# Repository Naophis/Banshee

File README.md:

# Banshee
 
2022年全日本大会で突貫で2セル化したExiaSnowWhiteをベースに、正式な2セル機として作成したシリーズ。  
ExiaSnowWhiteでは電源周りのノイズに苦戦した反省から回路の見直しを実施。  
足回りについてはマイクロマウス合宿で発表した「ベアリングホルダー方式」を採用することで、足回りの剛性を強化。高速走行時の安定性につなぐことができた機体です。

このリポジトリでは、Bansheeで利用しているすべてのソースコードと基板のファイルを公開しています。

## 利用部品解説

### 1. CPU
ESP32-S3の以下の型番を利用
* ESP32-S3-FH4R2 (Banshee/BansheeAlter)
* ESP32-S3-PICO-1 (Banshee.SSS)

上記の2モデルは昨年発売されておらず、今シーズンから採用。  
昨年使用していたESP32-S3-FN8との違いはPSRAMが搭載で、2MBまでログを取得できるようになったことで細かい解析ができるようになった。

ESP32-PICO-1ではオシレーターの内蔵版となったことで部品点数削減につながった。

画像の通りパッドに違いがある。

#### 1.1 困ったこと
#### 1.1.1 FreeRTOSの固着
ESP32-S3ではデータシートにオシレーターの推奨回路が提示されているが、そのとおり実装すると、モーターを高Dutyで回した際に、FreeRTOSが停止するという問題が発生、推奨回路のコンデンサを除去することで解決した。

#### 1.1.2 データシートにないピンの初期値High問題
書き込み時、電源投入時にHighを出力するピンが存在した。  
ESP32の他シリーズではデータシートに記載しているものもあるがS3では未記載である。
モータードライバにつながったピンに利用すると書き込み時にDuty100%で回転するなど、運用面の問題が発生するため回路の作り直しにつながった。

以下が問題のピン
* PIN26: GPIO20
* PIN28: GPIO26
* PIN44: GPIO39
> 他にもある可能性があり。

### 2. MotorDriver
* DRV8835  (Banshee/BansheeAlter)
* TB6614FNG (Banshee.SSS)

#### 2.1 DRV8835
多くの機体で採用されているが、その理由は以下の通り。
1. 小型ながら2A出力できるため、パフォーマンスが高い。
2. 内部抵抗が300mΩと低い
3. スイッチング周波数が最大250kHzと高く、モーターの特性に対応しやすい。
4. dead timeが100nsecと短いため、高めのPWM周波数に対応しやすい。
dead timeについては、大きい場合High-Lowの切り替えに時間がかかりすぎ、何も出力できないということがあり得る。同社の別のモータードライバでは同じような使い方をするとモーターが回らないということがあり得る。

しかし、最大定格が12Vまでであることから、3セルには対応できないため、TB6614FNGに切り替えた。

### 2.2 TB6614GNG
ディスコン部品であり、パッケージもSOP16と大きいが採用理由は以下の通り。
1. 定格が15Vと3セルに対応
2. 出力が瞬間最大4.5Aまで出力できる
3. スイッチング周波数が400kHzと非常に高く、モーターの特性に対応しやすい
4. dead timeが80nsecと短い

3セル化に伴い、クラシックで利用実績があったICであり、パワー勝負するために信頼できることから採用した。

### 3. PowerSupply
#### 3.1 LXDC55
2セル、3セルから直接3.3Vを取得する場合損失が大きく、熱による影響と効率の観点からDCDCコンバータを採用。入力側に容量が大きいコンデンサをつけないとノイズが乗りやすいため、高分子タンタルコンデンサを複数搭載することでノイズ問題は解決した。

> 約4.2Vを出力するよう、500Ωを利用。  

秋月にて購入できるため採用。

#### 3.2 MIC5319-3.3YM5
3.3V出力に利用。LEDの出力を大きくしたため、500mA出力できるこのICを採用。
データシート通りバイパス用のピンに470pFのコンデンサをつけることでノイズの低減効果がある。

秋月にて購入できるため採用。

### 4. LED + PhotoTransistor
* LED:
  * OSI5FU3A11C
  * VSLY5940
* PhotoTransistor: 
  * LTR-4206E

BCR421UFD（定電流回路）を使うことで安定したセンシングを狙っていたが、
昨年の全日本大会では会場の照明が近いことから、環境ノイズの影響を大きく受けた。  
今年も同じ会場になることから、SN比が良くなるよう、高出力化できる＋LTR-4206Eの帯域に合う大型LEDを採用した

#### 5. gyro
LSM6DSRXTRを採用。4000deg/sec対応している点、昨年のExiaSnowWhiteから継続採用

#### 6. encoder
AS5147Pを採用。14bit対応+28000RPMまで対応しているため継続採用。

ベアリングホルダー方式ではエンコーダ基板に穴を開けることで位置決めしやすいした。

## システム解説

Espressif社がESP32向けにカスタムしたFreeRTOSを利用。  
マイクロマウスでは一定周期で実行したい処理と非同期で実行したい処理が大きく分かれる、これらが混在すると周期に乱れが生じてしまう。ESP32-S3はCPUを2コア搭載していることから、物理的に分けて処理することでシステム全体を滞りなく動かすことを狙った設計となっている。

### 工夫
リアルタイムOSを利用しているとはいえ、タスクの優先順位次第では一定周期で処理できないことがある。特にエンコーダは前回値との差を使い速度を算出するため時刻差の影響を大きく受けた。

対策として、前回取得した時刻を記憶、現在時刻との差分から速度、距離の算出に利用したことで制御・判断の精度向上した。

### 課題

上記の画像は上側がplanning_task、下側がsensing_taskの処理時間(μsec)のログである。  
特にsensing_taskでは、定期的に1000μsecを大きく超え、周期が安定しないときが見られる。
また、planningのタスクの優先度を高く設定しているため、安定しているように見える。

原因は2つ判明しており、  
1つ目はmain_taskから要求される指示メッセージの処理不可が大きい点  
2つ目はセンサーに使用するAD変換に時間がかかる点  
である。

メッセージの送信自体が重くデータは構造体ではなく、ポインタを送信しているためデータ量に起因するものではないため、改善が難しい。
AD変換もESP32自体がIoT向けのマイコンである点からあまり得意でないことから改善が不可能である。

AD変換については、常にすべてのAD変換を行うのではなく、重要度の低いものは１回おきに取得することでシステム全体の負荷を下げるなどの工夫はしているが不十分な状況である。

いずれも今後発売予定のESP32-P4による性能向上に伴う改善を期待する。

## change log
1. Banshee
2. Banshee Alter
3. ~~(BansheeNorn)~~
4. Banshee.SSS　(latest)

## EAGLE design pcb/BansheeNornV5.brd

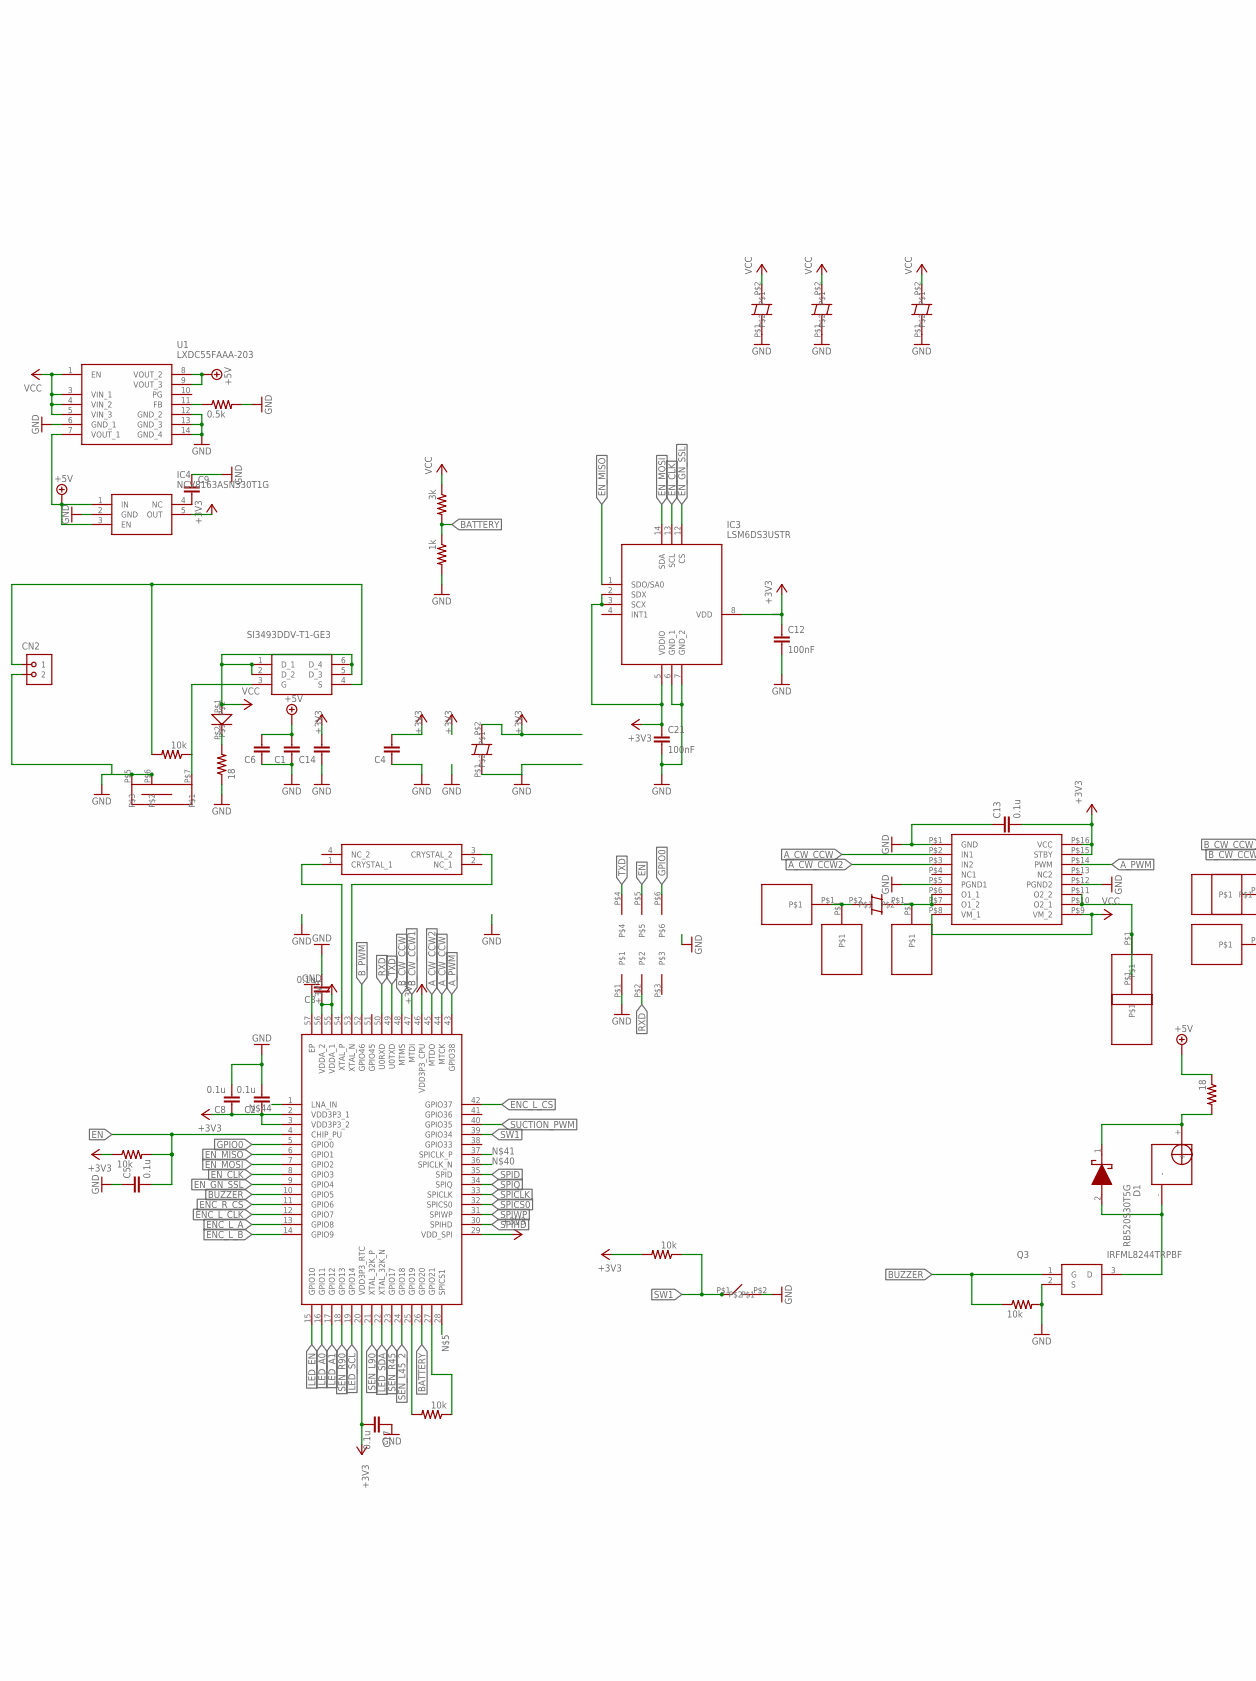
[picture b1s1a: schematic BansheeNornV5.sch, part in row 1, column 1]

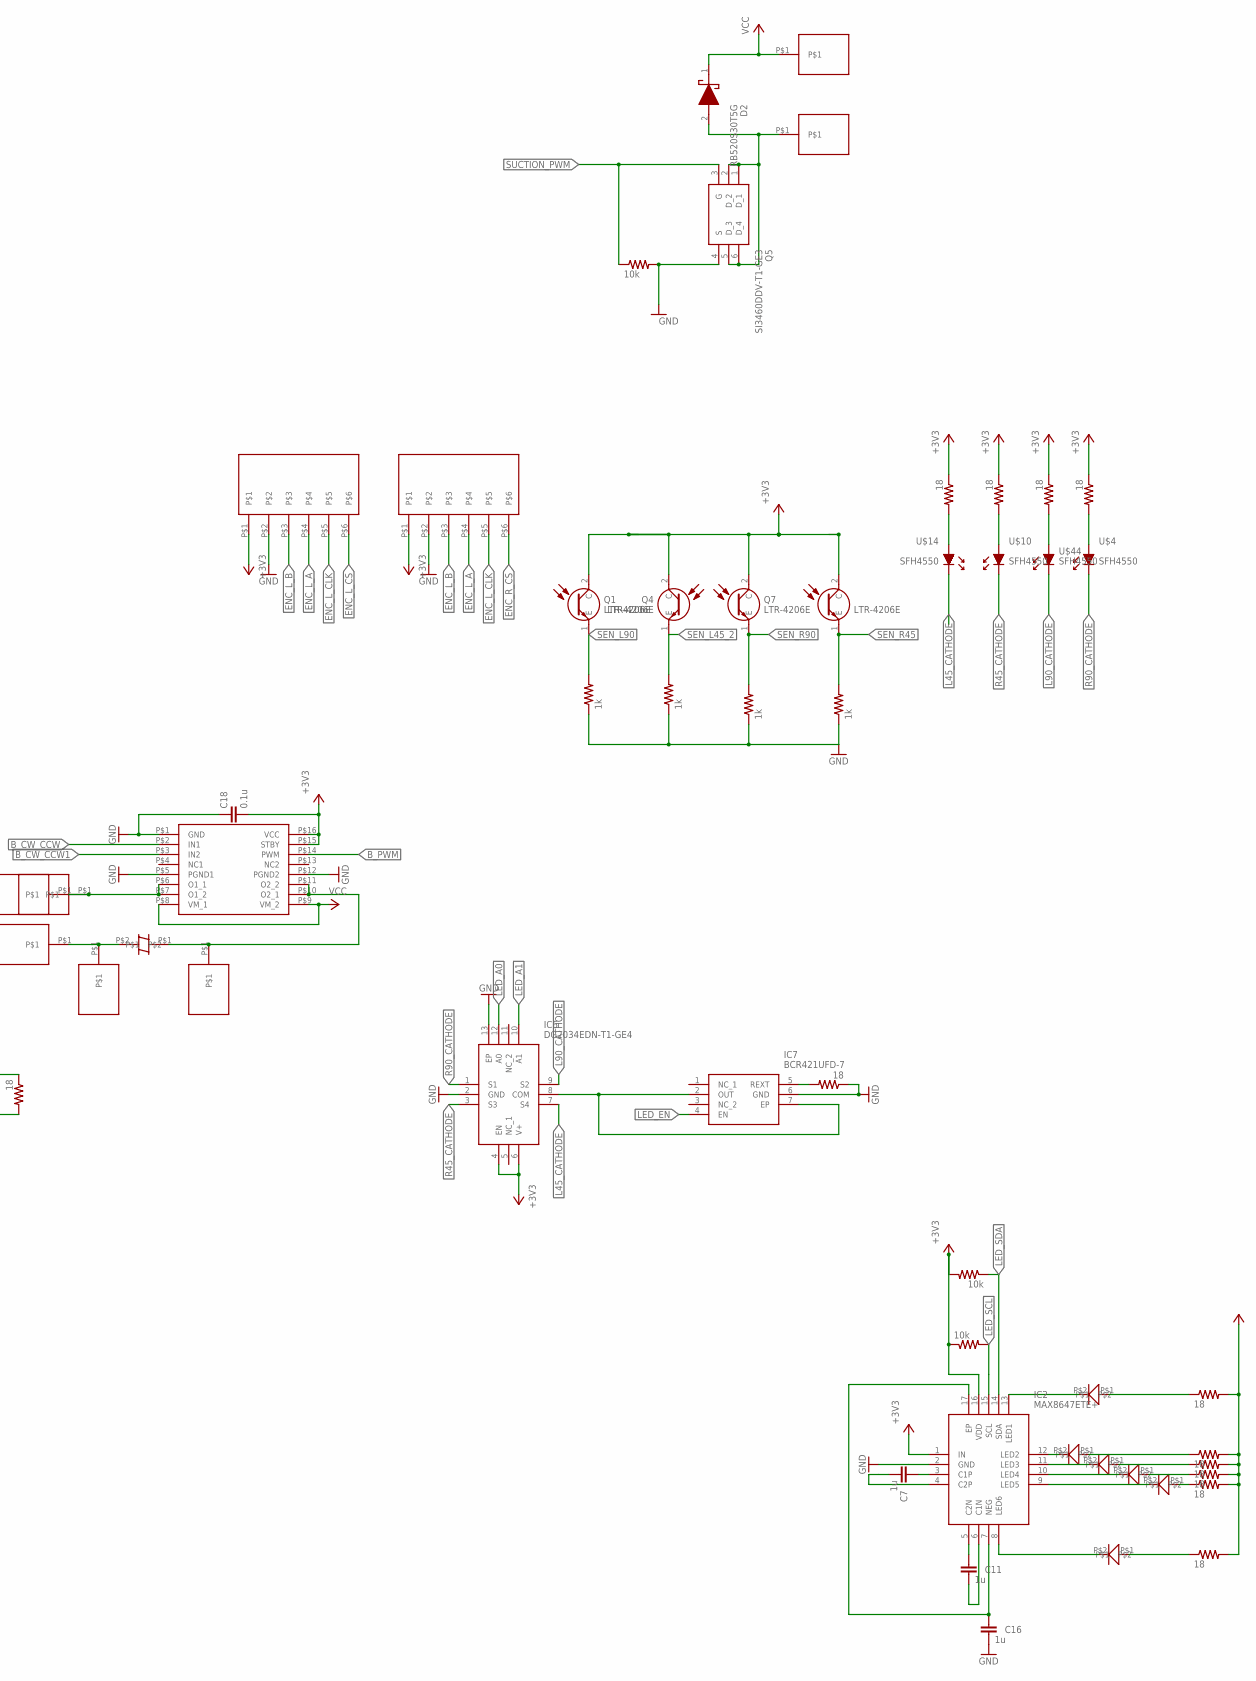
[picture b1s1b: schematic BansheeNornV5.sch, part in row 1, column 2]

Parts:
C1, C4, C6, C14: C3216
C2, C3, C5, C8, C13, C17, C18: 0.1u; R1005
C7, C11, C16: 1u; R1005
C9: C1608
C12, C21: 100nF; R1005
CN2: HRCON-2
D1, D2: RB520S30T5G; SODFL1608X70N
IC1: ESP32-S3-WROOM-1-N8; QFN40P700X700X90-57N
IC2: MAX8647ETE+; QFN50P300X300X80-17N
IC3: LSM6DS3USTR; LGA-14(2.5X3X0.86)
IC4: NCV8163ASN330T1G; SOT95P275X110-5N
IC6: DG2034EDN-T1-GE4; QFN50P300X300X100-13N
IC7: BCR421UFD-7; BCR421UFD7
Q1, Q4, Q7, Q8: LTR-4206E; LTR4206E
Q2: SI3493DDV-T1-GE3; SOT95P284X110-6N
Q3: IRFML8244TRPBF; SOT95P237X112-3N
Q5: SI3460DDV-T1-GE3; SOT95P284X110-6N
R1, R4, R7, R8, R9, R12, R13, R21: 10k; R1005
R2: 3k; R1005
R3, R16, R17, R18, R22: 1k; R1005
R5: 0.5k; R1005
R6, R10, R15, R19, R25, R26, R27, R28, R29, R30, R31, R32, R33: 18; R1608
U1: LXDC55FAAA-203; LXDC55FAAA203
U$1, U$8, U$9, U$11, U$17, U$20, U$26, U$27, U$29, U$32, U$57, U$58: PAD
U$2, U$19, U$21, U$23, U$25, U$30, U$31: LED_1005
U$3, U$5, U$7, U$12, U$16, U$24: PANA
U$4, U$10, U$14, U$44: SFH4550; SFH_4550
U$6: PIN2_3
U$13: BUZZER_44; BUZZER
U$15, U$28: ENCORDER_1; ENCORDER_R
U$18, U$22: TB6614
U$43: TVAF06
U$53: SWICH; SWITCH
Y1: XRCGB40M000F5A00R0; XRCGB32_F

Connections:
+3V3: C2.P$1 (1), C3.P$1 (1), C4.2, C8.P$1 (1), C12.P$1 (1), C13.P$2 (2), C14.2, C17.P$2 (2), C18.P$2 (2), C21.P$1 (1), IC1.2 (VDD3P3_1), IC1.3 (VDD3P3_2), IC1.20 (VDD3P3_RTC), IC1.29 (VDD_SPI), IC1.46 (VDD3P3_CPU), IC1.55 (VDDA_1), IC1.56 (VDDA_2), IC2.1 (IN), IC2.16 (VDD), IC3.2 (SDX), IC3.3 (SCX), IC3.5 (VDDIO), IC3.8 (VDD), IC4.5 (OUT), IC6.4 (EN), IC6.6 (V+), Q1.2 (C), Q4.2 (C), Q7.2 (C), Q8.2 (C), R1.P$1 (1), R8.P$2 (2), R12.P$1 (1), R13.P$2 (2), R15.1, R25.1, R26.1, R27.2, R28.2, R29.1, R30.2, R31.2, R32.2, R33.2, U$15.P$1, U$18.P$15 (STBY), U$18.P$16 (VCC), U$22.P$15 (STBY), U$22.P$16 (VCC), U$24.P$2, U$28.P$1
+5V: C1.2, C6.2, IC4.1 (IN), IC4.3 (EN), R10.1, U1.7 (VOUT_1), U1.8 (VOUT_2), U1.9 (VOUT_3)
A_CW_CCW: IC1.44 (MTCK), U$18.P$2 (IN1)
A_CW_CCW2: IC1.45 (MTDO), U$18.P$3 (IN2)
A_PWM: IC1.43 (GPIO38), U$18.P$14 (PWM)
BATTERY: IC1.26 (GPIO20), R2.P$2 (2), R3.P$1 (1)
BUZZER: IC1.10 (GPIO5), Q3.1 (G), R9.P$1 (1)
B_CW_CCW: IC1.48 (MTMS), U$22.P$2 (IN1)
B_CW_CCW1: IC1.47 (MTDI), U$22.P$3 (IN2)
B_PWM: IC1.52 (GPIO46), U$22.P$14 (PWM)
EN: C5.P$2 (2), IC1.4 (CHIP_PU), R1.P$2 (2), U$6.P$5
ENC_L_A: IC1.13 (GPIO8), U$15.P$4, U$28.P$4
ENC_L_B: IC1.14 (GPIO9), U$15.P$3, U$28.P$3
ENC_L_CLK: IC1.12 (GPIO7), U$15.P$5, U$28.P$5
ENC_L_CS: IC1.42 (GPIO37), U$15.P$6
ENC_R_CS: IC1.11 (GPIO6), U$28.P$6
EN_CLK: IC1.8 (GPIO3), IC3.13 (SCL)
EN_GN_SSL: IC1.9 (GPIO4), IC3.12 (CS)
EN_MISO: IC1.6 (GPIO1), IC3.1 (SDO/SA0)
EN_MOSI: IC1.7 (GPIO2), IC3.14 (SDA)
GND: C1.1, C2.P$2 (2), C3.P$2 (2), C4.1, C5.P$1 (1), C6.1, C8.P$2 (2), C9.1, C12.P$2 (2), C13.P$1 (1), C14.1, C16.P$2 (2), C17.P$1 (1), C18.P$1 (1), C21.P$2 (2), CN2.2, IC1.57 (EP), IC2.2 (GND), IC3.6 (GND_1), IC3.7 (GND_2), IC4.2 (GND), IC6.2 (GND), IC6.13 (EP), IC7.6 (GND), Q3.2 (S), Q5.4 (S), R3.P$2 (2), R5.P$2 (2), R6.1, R9.P$2 (2), R16.P$1 (1), R17.P$1 (1), R18.P$1 (1), R19.1, R21.P$2 (2), R22.P$1 (1), U1.6 (GND_1), U1.12 (GND_2), U1.13 (GND_3), U1.14 (GND_4), U$5.P$1, U$6.P$1, U$12.P$1, U$15.P$2, U$16.P$1, U$18.P$1 (GND), U$18.P$5 (PGND1), U$18.P$12 (PGND2), U$22.P$1 (GND), U$22.P$5 (PGND1), U$22.P$12 (PGND2), U$24.P$1, U$28.P$2, U$43.P$2, U$53.P$5, U$53.P$6
GPIO0: IC1.5 (GPIO0), U$6.P$6
L45_CATHODE: IC6.7 (S4), U$14.CASODE (K)
L90_CATHODE: IC6.9 (S2), U$44.CASODE (K)
LED_A0: IC1.16 (GPIO11), IC6.12 (A0)
LED_A1: IC1.17 (GPIO12), IC6.10 (A1)
LED_EN: IC1.15 (GPIO10), IC7.4 (EN)
LED_SCL: IC1.19 (GPIO14), IC2.15 (SCL), R12.P$2 (2)
LED_SDA: IC1.22 (XTAL_32K_N), IC2.14 (SDA), R13.P$1 (1)
unnamed: D1.1 (K), R10.2, U$13.+
unnamed: IC6.8 (COM), IC7.2 (OUT), IC7.7 (EP)
unnamed: D1.2 (A), Q3.3 (D), U$13.-
unnamed: R6.2, U$2.P$2
unnamed: U$3.P$1, U$9.P$1, U$18.P$6 (O1_1), U$18.P$7 (O1_2)
unnamed: R33.1, U$30.P$1
unnamed: R32.1, U$23.P$1
unnamed: R31.1, U$21.P$1
unnamed: R30.1, U$19.P$1
unnamed: R28.1, U$25.P$1
unnamed: IC1.25 (GPIO19), R4.P$2 (2)
unnamed: U$7.P$1, U$17.P$1, U$22.P$10 (O2_1), U$22.P$11 (O2_2)
unnamed: R27.1, U$31.P$1
unnamed: Q2.3 (G), R7.P$1 (1), U$53.P$7
unnamed: C9.2, IC4.4 (NC)
unnamed: CN2.1, Q2.4 (S), R7.P$2 (2)
unnamed: R29.2, U$14.ANODE (A)
unnamed: R15.2, U$10.ANODE (A)
unnamed: R25.2, U$44.ANODE (A)
unnamed: R26.2, U$4.ANODE (A)
unnamed: IC1.27 (GPIO21), R4.P$1 (1)
unnamed: U$3.P$2, U$11.P$1, U$27.P$1
unnamed: U$7.P$2, U$26.P$1, U$57.P$1
unnamed: IC7.5 (REXT), R19.2
unnamed: R5.P$1 (1), U1.11 (FB)
unnamed: D2.2 (A), Q5.1 (D_1), Q5.2 (D_2), Q5.5 (D_3), Q5.6 (D_4), U$58.P$1
unnamed: IC1.54 (XTAL_P), Y1.1 (CRYSTAL_1)
unnamed: IC1.53 (XTAL_N), Y1.3 (CRYSTAL_2)
unnamed: U$1.P$1, U$18.P$10 (O2_1), U$18.P$11 (O2_2), U$32.P$1
unnamed: U$8.P$1, U$22.P$6 (O1_1), U$22.P$7 (O1_2), U$29.P$1
unnamed: C7.P$1 (1), IC2.3 (C1P)
unnamed: C7.P$2 (2), IC2.4 (C2P)
unnamed: C11.P$1 (1), IC2.5 (C2N)
unnamed: C11.P$2 (2), IC2.6 (C1N)
unnamed: C16.P$1 (1), IC2.7 (NEG), IC2.17 (EP)
unnamed: IC2.8 (LED6), U$31.P$2
unnamed: IC2.13 (LED1), U$30.P$2
unnamed: IC2.12 (LED2), U$23.P$2
unnamed: IC2.11 (LED3), U$21.P$2
unnamed: IC2.10 (LED4), U$19.P$2
unnamed: IC2.9 (LED5), U$25.P$2
R45_CATHODE: IC6.3 (S3), U$10.CASODE (K)
R90_CATHODE: IC6.1 (S1), U$4.CASODE (K)
RXD: IC1.50 (U0RXD), U$6.P$2
SEN_L45_2: IC1.24 (GPIO18), Q4.1 (E), R17.P$2 (2)
SEN_L90: IC1.21 (XTAL_32K_P), Q1.1 (E), R18.P$2 (2)
SEN_R45: IC1.23 (GPIO17), Q8.1 (E), R16.P$2 (2)
SEN_R90: IC1.18 (GPIO13), Q7.1 (E), R22.P$2 (2)
SPICLK: IC1.33 (SPICLK)
SPICS0: IC1.32 (SPICS0)
SPID: IC1.35 (SPID)
SPIHD: IC1.30 (SPIHD)
SPIQ: IC1.34 (SPIQ)
SPIWP: IC1.31 (SPIWP)
SUCTION_PWM: IC1.40 (GPIO35), Q5.3 (G), R21.P$1 (1)
SW1: IC1.39 (GPIO34), R8.P$1 (1), U$43.P$1
TXD: IC1.49 (U0TXD), U$6.P$4
VCC: D2.1 (K), Q2.1 (D_1), Q2.2 (D_2), Q2.5 (D_3), Q2.6 (D_4), R2.P$1 (1), U1.1 (EN), U1.3 (VIN_1), U1.4 (VIN_2), U1.5 (VIN_3), U$2.P$1, U$5.P$2, U$12.P$2, U$16.P$2, U$18.P$8 (VM_1), U$18.P$9 (VM_2), U$20.P$1, U$22.P$8 (VM_1), U$22.P$9 (VM_2)

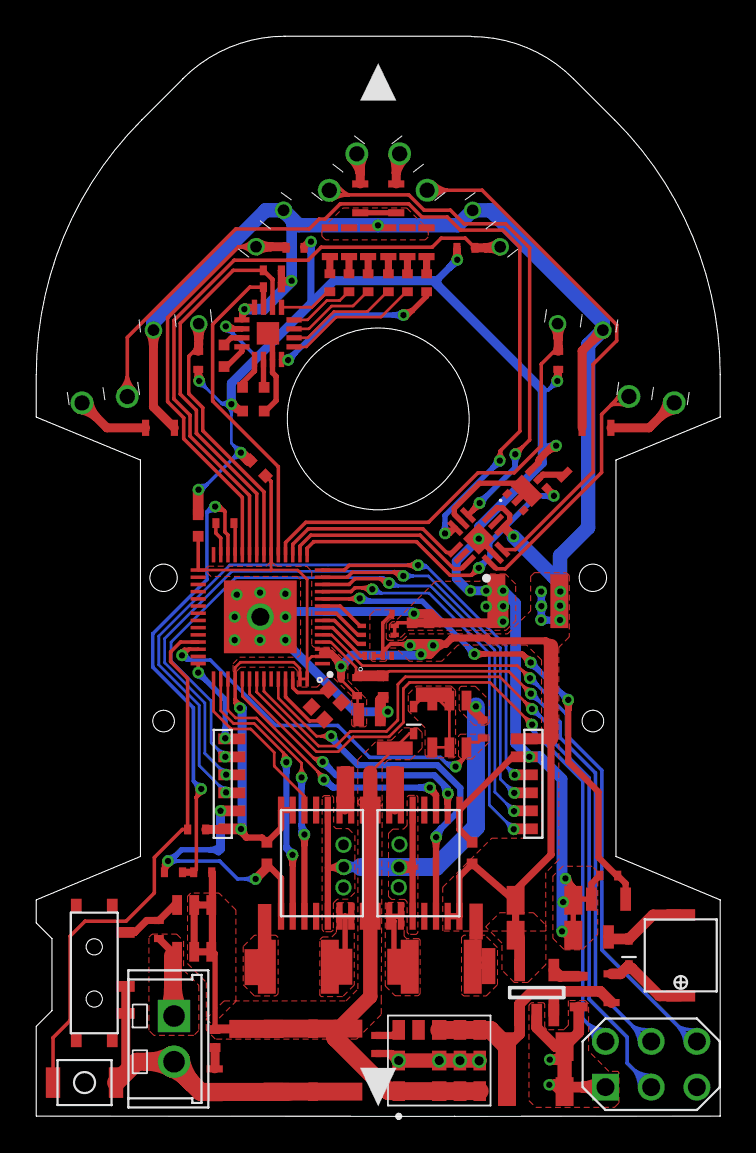
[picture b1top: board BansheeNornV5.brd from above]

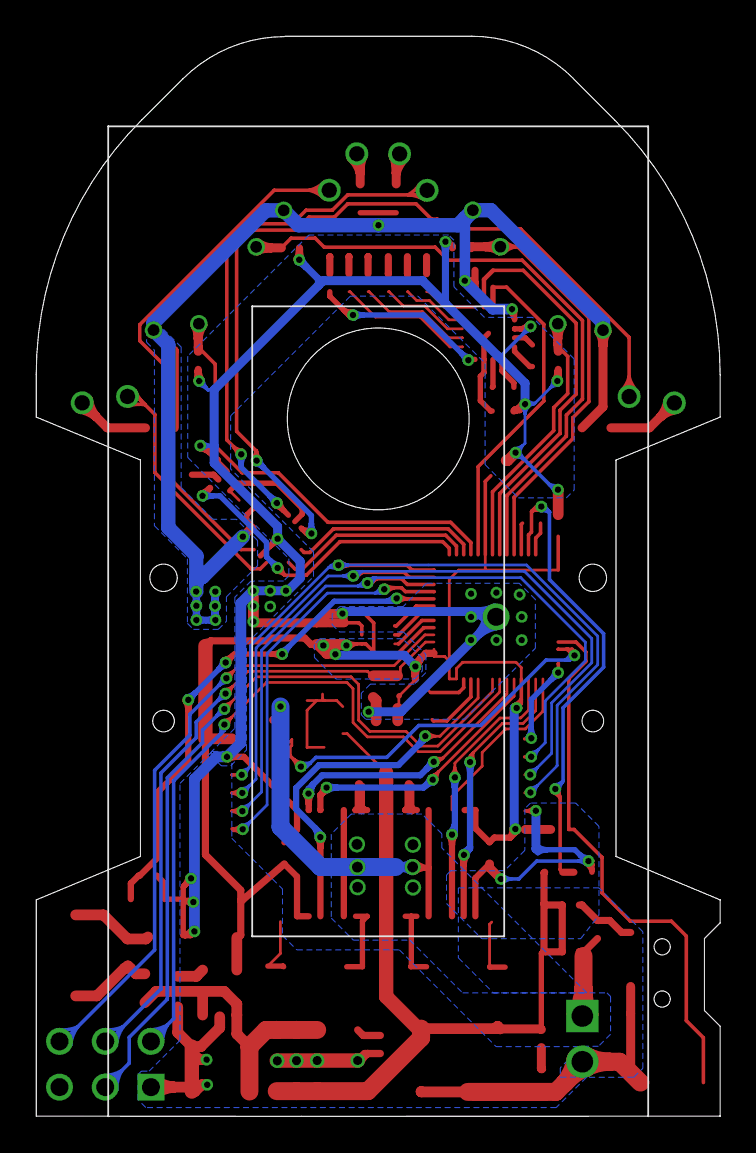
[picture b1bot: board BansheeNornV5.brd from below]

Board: 2 copper layers, 38.0 x 60.0 mm, 100 parts (2 on the bottom side), 81 nets.

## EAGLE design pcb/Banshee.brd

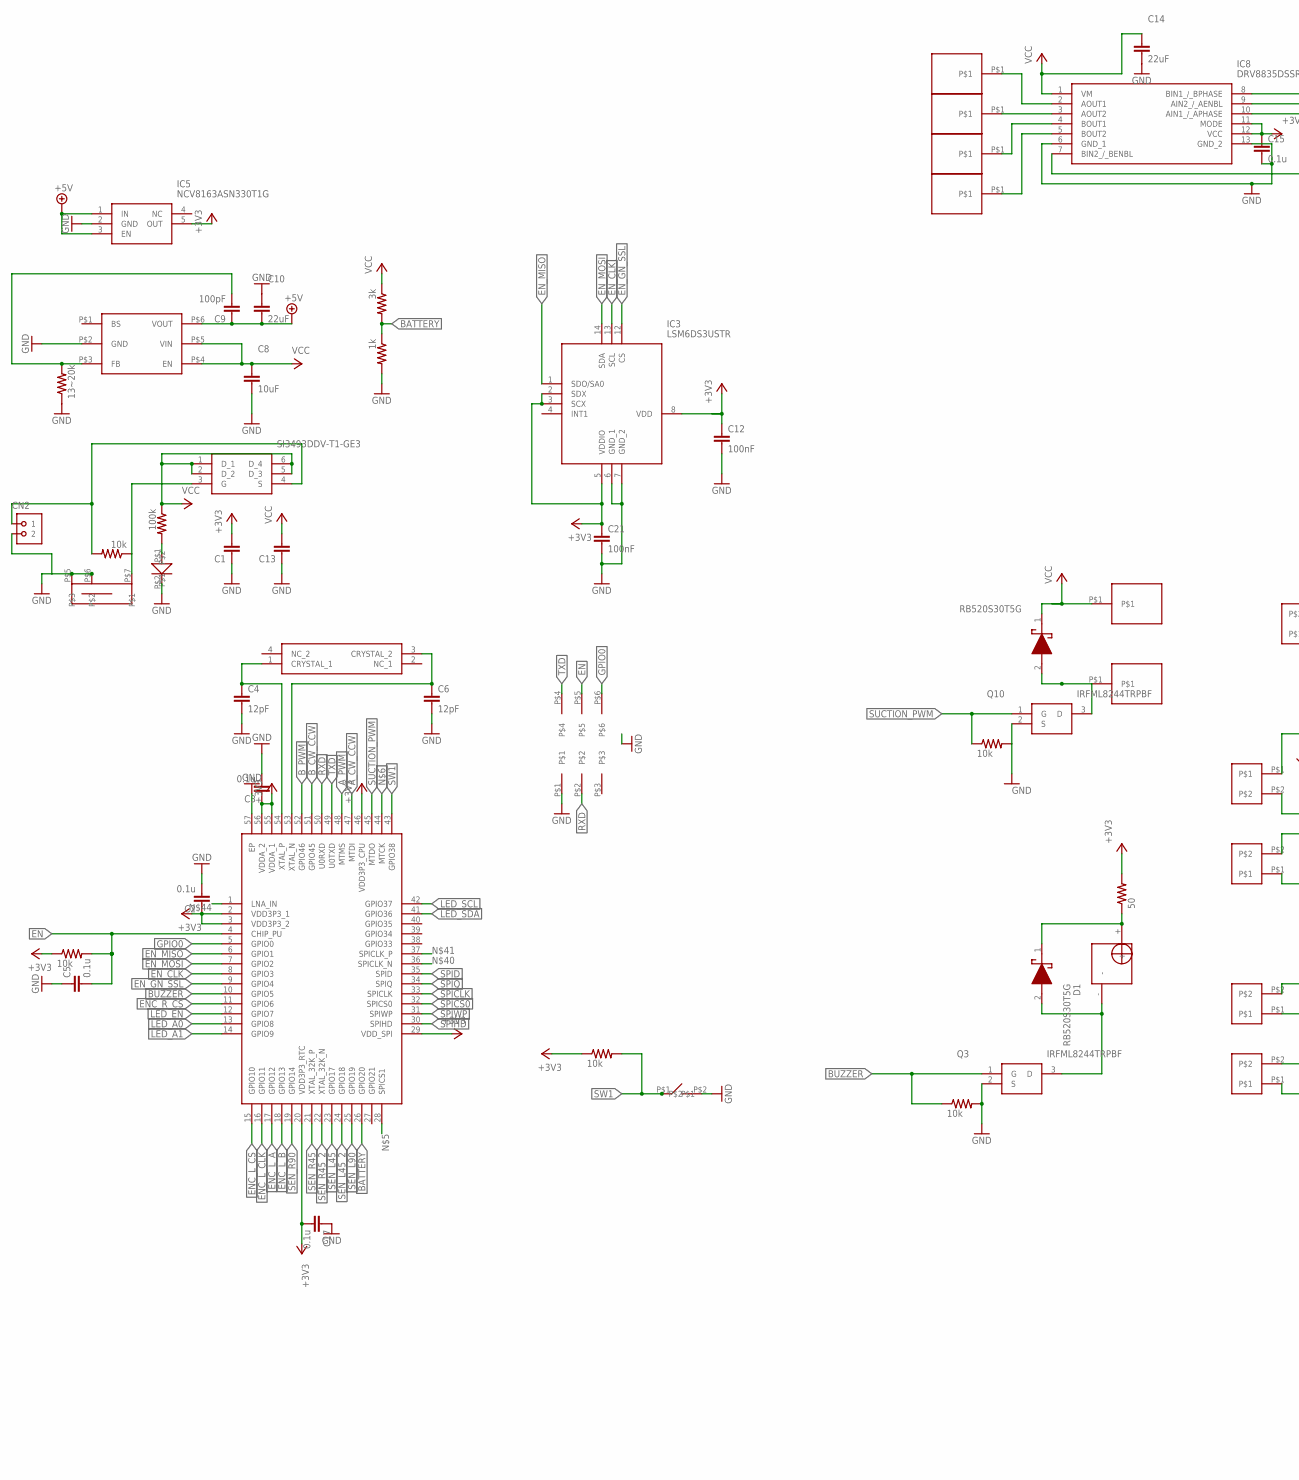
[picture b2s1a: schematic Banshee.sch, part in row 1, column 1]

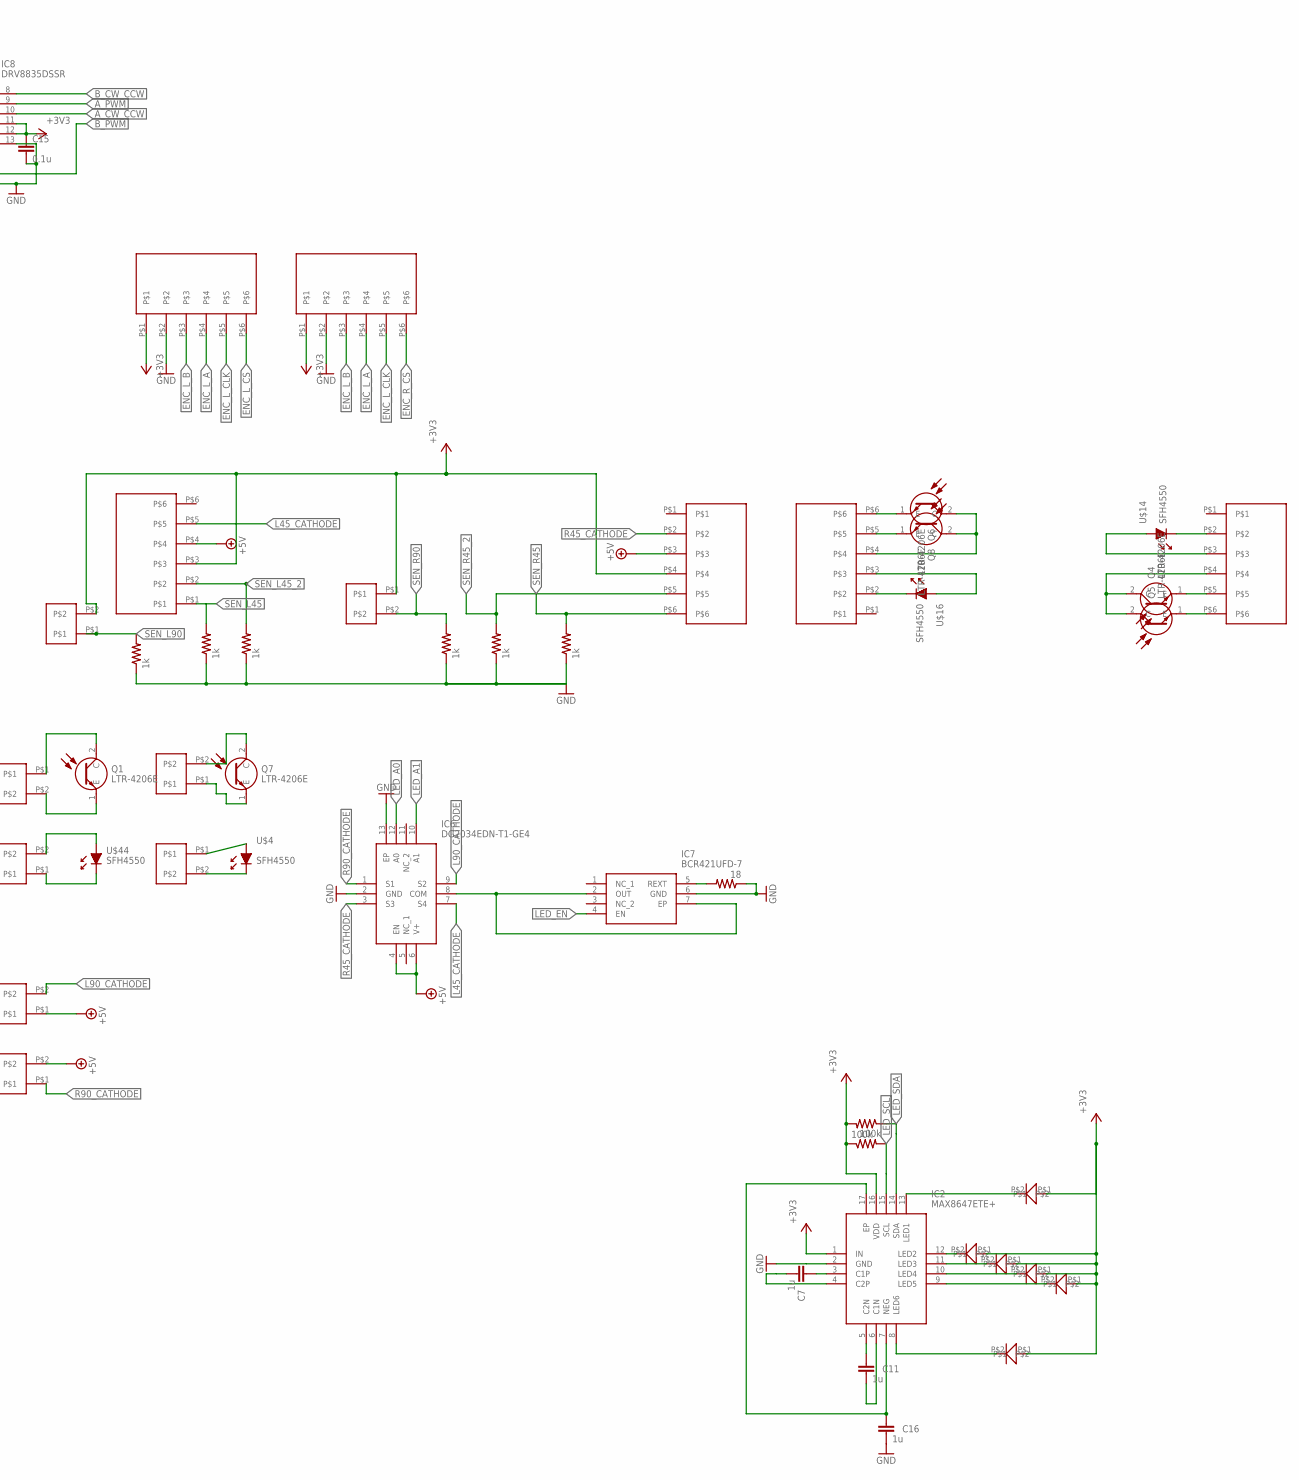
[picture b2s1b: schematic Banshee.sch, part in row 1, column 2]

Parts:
C1, C13: C3216
C2, C3, C5, C15, C17: 0.1u; R1005
C4, C6: 12pF; R1005
C7, C11, C16: 1u; R1005
C8: 10uF; C3216
C9: 100pF; R1005
C10, C14: 22uF; C3216
C12, C21: 100nF; R1005
CN2: HRCON-2
D1, D2: RB520S30T5G; SODFL1608X70N
IC1: ESP32-S3-WROOM-1-N8; QFN40P700X700X90-57N
IC2: MAX8647ETE+; QFN50P300X300X80-17N
IC3: LSM6DS3USTR; LGA-14(2.5X3X0.86)
IC5: NCV8163ASN330T1G; SOT95P275X110-5N
IC6: DG2034EDN-T1-GE4; QFN50P300X300X100-13N
IC7: BCR421UFD-7; BCR421UFD7
IC8: DRV8835DSSR
Q1, Q4, Q5, Q6, Q7, Q8: LTR-4206E; LTR4206E
Q2: SI3493DDV-T1-GE3; SOT95P284X110-6N
Q3, Q10: IRFML8244TRPBF; SOT95P237X112-3N
R1, R7, R8, R9, R10: 10k; R1005
R2: 3k; R1005
R3, R15, R16, R17, R18, R21, R22: 1k; R1005
R4, R12, R13: 100k; R1005
R5: 50; R1005
R19: 18; R1608
R25: 13~20k; R1005
U$1, U$5, U$7, U$8, U$9, U$11, U$17, U$20: SENSOR_FRONT_PAD2
U$2, U$19, U$21, U$23, U$25, U$30, U$31: LED_1005
U$3: MUN12AD01-SG
U$4, U$14, U$16, U$44: SFH4550; SFH_4550
U$6: PIN2_3
U$10, U$12, U$15, U$22, U$24, U$28: ENCORDER_1; ENCORDER_R
U$13: BUZZER_44; BUZZER
U$18, U$26, U$27, U$29, U$57, U$58: PAD
U$43: TVAF06
U$53: SWICH; SWITCH
Y1: XRCGB40M000F5A00R0; XRCGB32_F

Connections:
+3V3: C1.2, C2.P$1 (1), C3.P$1 (1), C12.P$1 (1), C15.P$1 (1), C17.P$2 (2), C21.P$1 (1), IC1.2 (VDD3P3_1), IC1.3 (VDD3P3_2), IC1.20 (VDD3P3_RTC), IC1.29 (VDD_SPI), IC1.46 (VDD3P3_CPU), IC1.55 (VDDA_1), IC1.56 (VDDA_2), IC2.1 (IN), IC2.16 (VDD), IC3.2 (SDX), IC3.3 (SCX), IC3.5 (VDDIO), IC3.8 (VDD), IC5.5 (OUT), IC8.11 (MODE), IC8.12 (VCC), R1.P$1 (1), R5.P$2 (2), R8.P$1 (1), R12.P$1 (1), R13.P$2 (2), U$5.P$1, U$7.P$2, U$15.P$1, U$19.P$1, U$21.P$1, U$22.P$3, U$23.P$1, U$24.P$4, U$25.P$1, U$28.P$1, U$30.P$1, U$31.P$1
+5V: C9.P$1 (1), C10.2, IC5.1 (IN), IC5.3 (EN), IC6.4 (EN), IC6.6 (V+), U$3.P$6 (VOUT), U$8.P$1, U$20.P$2, U$22.P$4, U$24.P$3
A_CW_CCW: IC1.47 (MTDI), IC8.10 (AIN1_/_APHASE)
A_PWM: IC1.48 (MTMS), IC8.9 (AIN2_/_AENBL)
BATTERY: IC1.26 (GPIO20), R2.P$2 (2), R3.P$1 (1)
BUZZER: IC1.10 (GPIO5), Q3.1 (G), R9.P$1 (1)
B_CW_CCW: IC1.51 (GPIO45), IC8.8 (BIN1_/_BPHASE)
B_PWM: IC1.52 (GPIO46), IC8.7 (BIN2_/_BENBL)
EN: C5.P$2 (2), IC1.4 (CHIP_PU), R1.P$2 (2), U$6.P$5
ENC_L_A: IC1.17 (GPIO12), U$15.P$4, U$28.P$4
ENC_L_B: IC1.18 (GPIO13), U$15.P$3, U$28.P$3
ENC_L_CLK: IC1.16 (GPIO11), U$15.P$5, U$28.P$5
ENC_L_CS: IC1.15 (GPIO10), U$15.P$6
ENC_R_CS: IC1.11 (GPIO6), U$28.P$6
EN_CLK: IC1.8 (GPIO3), IC3.13 (SCL)
EN_GN_SSL: IC1.9 (GPIO4), IC3.12 (CS)
EN_MISO: IC1.6 (GPIO1), IC3.1 (SDO/SA0)
EN_MOSI: IC1.7 (GPIO2), IC3.14 (SDA)
GND: C1.1, C2.P$2 (2), C3.P$2 (2), C4.P$2 (2), C5.P$1 (1), C6.P$2 (2), C8.2, C10.1, C12.P$2 (2), C13.1, C14.2, C15.P$2 (2), C16.P$2 (2), C17.P$1 (1), C21.P$2 (2), CN2.2, IC1.57 (EP), IC2.2 (GND), IC3.6 (GND_1), IC3.7 (GND_2), IC5.2 (GND), IC6.2 (GND), IC6.13 (EP), IC7.6 (GND), IC8.6 (GND_1), IC8.13 (GND_2), Q3.2 (S), Q10.2 (S), R3.P$2 (2), R9.P$2 (2), R10.P$2 (2), R15.P$1 (1), R16.P$1 (1), R17.P$1 (1), R18.P$1 (1), R19.1, R21.P$1 (1), R22.P$1 (1), R25.P$1 (1), U$2.P$2, U$3.P$2 (GND), U$6.P$1, U$15.P$2, U$28.P$2, U$43.P$2, U$53.P$5, U$53.P$6
GPIO0: IC1.5 (GPIO0), U$6.P$6
L45_CATHODE: IC6.7 (S4), U$22.P$5
L90_CATHODE: IC6.9 (S2), U$8.P$2
LED_A0: IC1.13 (GPIO8), IC6.12 (A0)
LED_A1: IC1.14 (GPIO9), IC6.10 (A1)
LED_EN: IC1.12 (GPIO7), IC7.4 (EN)
LED_SCL: IC1.42 (GPIO37), IC2.15 (SCL), R12.P$2 (2)
LED_SDA: IC1.41 (GPIO36), IC2.14 (SDA), R13.P$1 (1)
unnamed: D1.1 (K), R5.P$1 (1), U$13.+
unnamed: IC6.8 (COM), IC7.2 (OUT), IC7.7 (EP)
unnamed: D1.2 (A), Q3.3 (D), U$13.-
unnamed: R4.P$2 (2), U$2.P$1
unnamed: Q1.2 (C), U$1.P$1
unnamed: Q1.1 (E), U$1.P$2
unnamed: U$9.P$2, U$44.ANODE (A)
unnamed: U$9.P$1, U$44.CASODE (K)
unnamed: IC8.3 (AOUT2), U$26.P$1
unnamed: IC8.4 (BOUT1), U$27.P$1
unnamed: Q5.1 (E), U$12.P$6
unnamed: Q2.3 (G), R7.P$1 (1), U$53.P$7
unnamed: Q4.1 (E), U$12.P$5
unnamed: CN2.1, Q2.4 (S), R7.P$2 (2)
unnamed: Q4.2 (C), Q5.2 (C), U$12.P$4
unnamed: D2.2 (A), Q10.3 (D), U$58.P$1
unnamed: U$10.P$2, U$16.CASODE (K)
unnamed: U$12.P$3, U$14.ANODE (A)
unnamed: Q6.1 (E), U$10.P$6
unnamed: IC7.5 (REXT), R19.2
unnamed: U$4.ANODE (A), U$17.P$1
unnamed: Q8.1 (E), U$10.P$5
unnamed: C9.P$2 (2), R25.P$2 (2), U$3.P$3 (FB)
unnamed: U$4.CASODE (K), U$17.P$2
unnamed: IC8.2 (AOUT1), U$29.P$1
unnamed: Q7.1 (E), U$11.P$1
unnamed: C4.P$1 (1), IC1.54 (XTAL_P), Y1.1 (CRYSTAL_1)
unnamed: C6.P$1 (1), IC1.53 (XTAL_N), Y1.3 (CRYSTAL_2)
unnamed: Q7.2 (C), U$11.P$2
unnamed: Q6.2 (C), Q8.2 (C), U$10.P$4
unnamed: U$12.P$2, U$14.CASODE (K)
unnamed: U$10.P$3, U$16.ANODE (A)
unnamed: C7.P$1 (1), IC2.3 (C1P)
unnamed: C7.P$2 (2), IC2.4 (C2P)
unnamed: C11.P$1 (1), IC2.5 (C2N)
unnamed: C11.P$2 (2), IC2.6 (C1N)
unnamed: C16.P$1 (1), IC2.7 (NEG), IC2.17 (EP)
unnamed: IC2.8 (LED6), U$31.P$2
unnamed: IC2.13 (LED1), U$30.P$2
unnamed: IC2.12 (LED2), U$23.P$2
unnamed: IC2.11 (LED3), U$21.P$2
unnamed: IC2.10 (LED4), U$19.P$2
unnamed: IC2.9 (LED5), U$25.P$2
unnamed: IC8.5 (BOUT2), U$57.P$1
R45_CATHODE: IC6.3 (S3), U$24.P$2
R90_CATHODE: IC6.1 (S1), U$20.P$1
RXD: IC1.50 (U0RXD), U$6.P$2
SEN_L45: IC1.23 (GPIO17), R17.P$2 (2), U$22.P$1
SEN_L45_2: IC1.24 (GPIO18), R21.P$2 (2), U$22.P$2
SEN_L90: IC1.25 (GPIO19), R18.P$2 (2), U$7.P$1
SEN_R45: IC1.21 (XTAL_32K_P), R16.P$2 (2), U$24.P$6
SEN_R45_2: IC1.22 (XTAL_32K_N), R15.P$2 (2), U$24.P$5
SEN_R90: IC1.19 (GPIO14), R22.P$2 (2), U$5.P$2
SPICLK: IC1.33 (SPICLK)
SPICS0: IC1.32 (SPICS0)
SPID: IC1.35 (SPID)
SPIHD: IC1.30 (SPIHD)
SPIQ: IC1.34 (SPIQ)
SPIWP: IC1.31 (SPIWP)
SUCTION_PWM: IC1.45 (MTDO), Q10.1 (G), R10.P$1 (1)
SW1: IC1.43 (GPIO38), R8.P$2 (2), U$43.P$1
TXD: IC1.49 (U0TXD), U$6.P$4
VCC: C8.1, C13.2, C14.1, D2.1 (K), IC8.1 (VM), Q2.1 (D_1), Q2.2 (D_2), Q2.5 (D_3), Q2.6 (D_4), R2.P$1 (1), R4.P$1 (1), U$3.P$4 (EN), U$3.P$5 (VIN), U$18.P$1

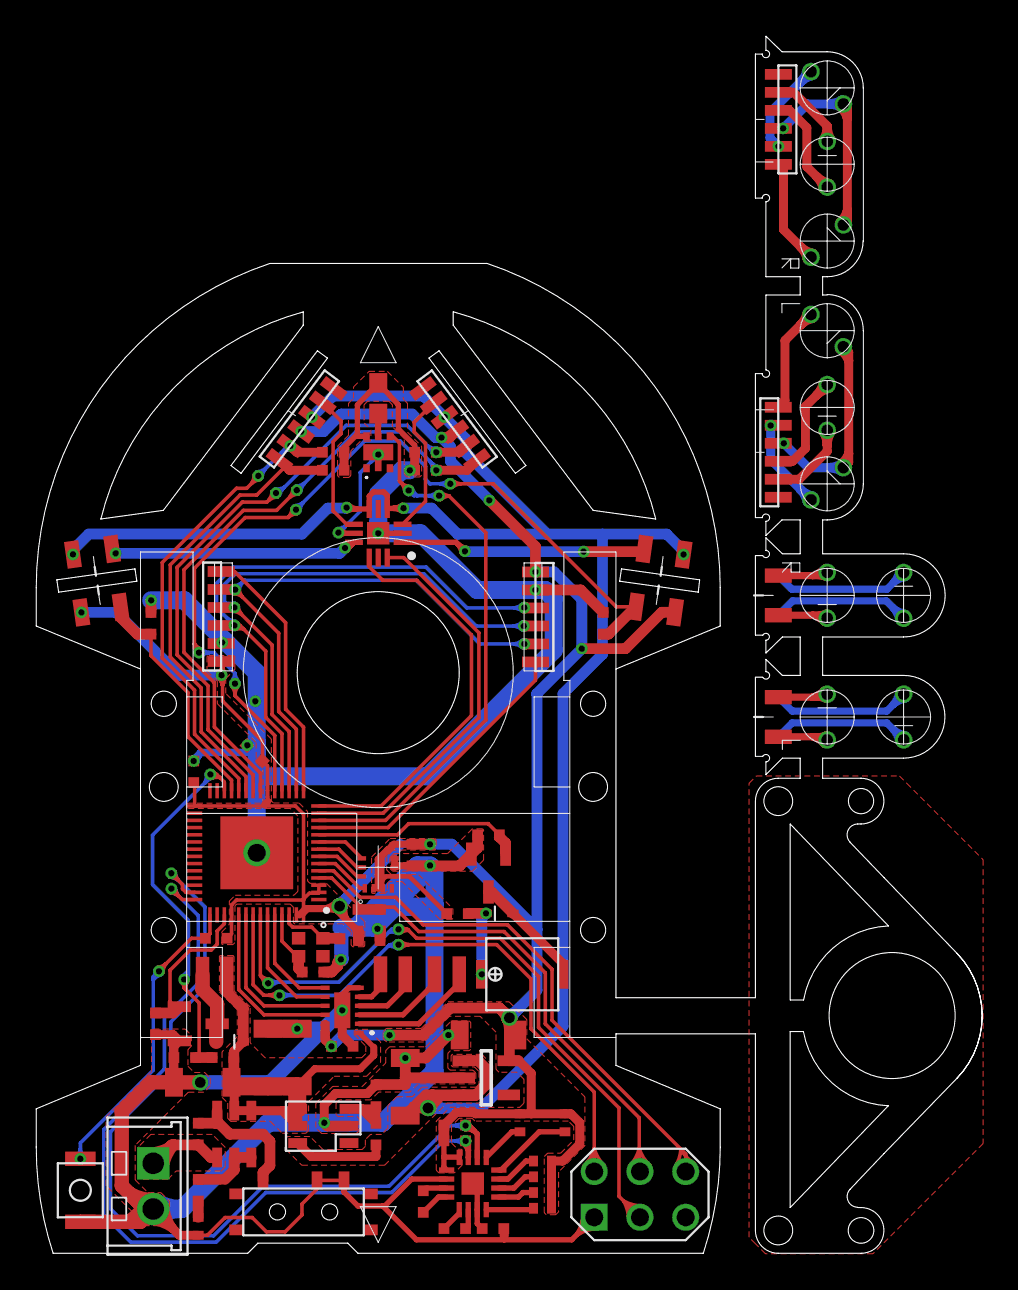
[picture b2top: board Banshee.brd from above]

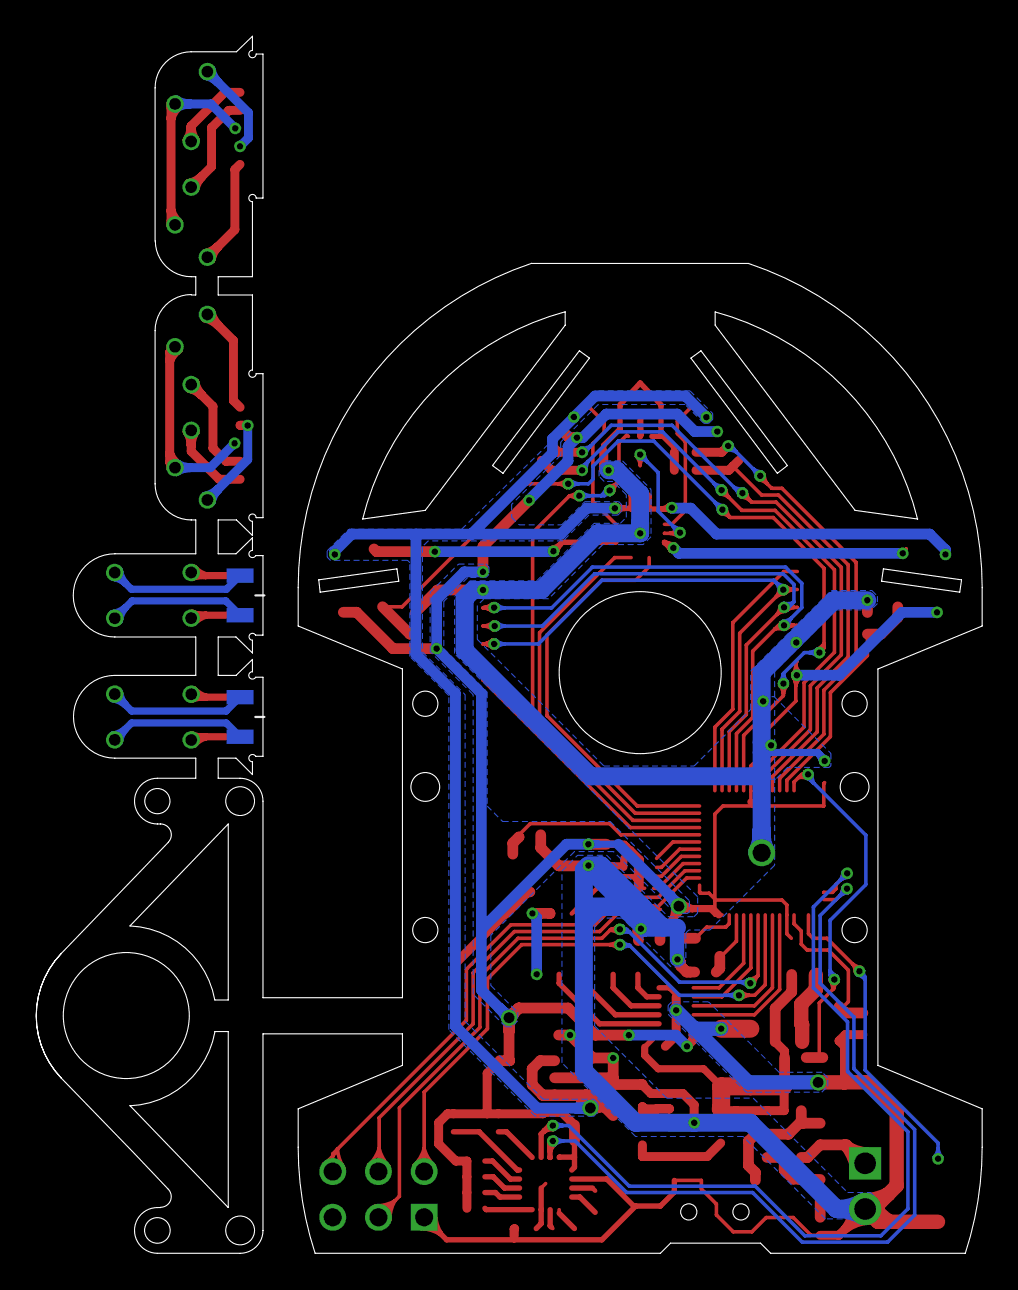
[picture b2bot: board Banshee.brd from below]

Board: 2 copper layers, 52.6 x 67.6 mm, 93 parts (4 on the bottom side), 84 nets.

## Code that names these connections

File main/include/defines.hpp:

#ifndef DEFINES_HPP
#define DEFINES_HPP

#include "driver/gpio.h"
#include "driver/ledc.h"
#include "gen_code_mpc/bus.h"
#include "include/maze_solver.hpp"
#include "sdkconfig.h"
#include "soc/adc_channel.h"
#include "soc/gpio_struct.h"
#include "soc/ledc_periph.h"

#include "fs.hpp"
#include "include/enums.hpp"
#include "include/structs.hpp"
#include "sdkconfig.h"
#include <bitset>
#include <initializer_list>
#include <iostream>
#include <memory>
#include <sstream>
#include <string>
#include <string_view>
#include <unordered_map>
#include <vector>

#include "esp_heap_caps.h"
#include "icm20689.hpp"
#include "lsm6dsr.hpp"

#define portTICK_RATE_MS portTICK_PERIOD_MS
#define xTaskHandle TaskHandle_t

#define ABS(IN) ((IN) < 0 ? -(IN) : (IN))

constexpr int GY_DQ_SIZE = 2;
constexpr int GY_CYCLE = 2500; // 2500=1/4msec
// constexpr int GY_CYCLE = 1250; // 1250=1/8msec
constexpr int GY_MODE = 0;
constexpr float cell_size = 90;

constexpr gpio_num_t SDA_PIN = GPIO_NUM_16;
constexpr gpio_num_t SCL_PIN = GPIO_NUM_14;

constexpr gpio_num_t LED_EN = GPIO_NUM_10;
constexpr gpio_num_t LED_A0 = GPIO_NUM_11;
constexpr gpio_num_t LED_A1 = GPIO_NUM_12;

constexpr gpio_num_t TXD = GPIO_NUM_43;
constexpr gpio_num_t RXD = GPIO_NUM_44;
constexpr gpio_num_t RTS = GPIO_NUM_15;
constexpr gpio_num_t CTS = GPIO_NUM_16;

constexpr gpio_num_t L_CW_CCW1 = GPIO_NUM_39;
constexpr gpio_num_t L_CW_CCW2 = GPIO_NUM_40;
constexpr gpio_num_t R_CW_CCW1 = GPIO_NUM_41;
constexpr gpio_num_t R_CW_CCW2 = GPIO_NUM_42;

constexpr uint32_t L_CW_CCW1_BIT = BIT(GPIO_NUM_39 - 32);
constexpr uint32_t L_CW_CCW2_BIT = BIT(GPIO_NUM_40 - 32);
constexpr uint32_t R_CW_CCW1_BIT = BIT(GPIO_NUM_41 - 32);
constexpr uint32_t R_CW_CCW2_BIT = BIT(GPIO_NUM_42 - 32);

constexpr gpio_num_t Motor_L_PWM = GPIO_NUM_38;
constexpr gpio_num_t Motor_L_PWM2 = GPIO_NUM_38;
constexpr gpio_num_t Motor_R_PWM = GPIO_NUM_46;
constexpr gpio_num_t Motor_R_PWM2 = GPIO_NUM_46;

constexpr gpio_num_t BUZZER = GPIO_NUM_5;

constexpr gpio_num_t SW1 = GPIO_NUM_34;

constexpr gpio_num_t EN_MISO = GPIO_NUM_1;
constexpr gpio_num_t EN_MOSI = GPIO_NUM_2;
constexpr gpio_num_t EN_CLK = GPIO_NUM_3;
constexpr gpio_num_t EN_GN_SSL = GPIO_NUM_4;

constexpr gpio_num_t ENC_R_CS = GPIO_NUM_6;
constexpr gpio_num_t ENC_L_CS = GPIO_NUM_37;
constexpr gpio_num_t ENC_CLK = GPIO_NUM_7;
constexpr gpio_num_t ENC_MISO = GPIO_NUM_8; // B
constexpr gpio_num_t ENC_MOSI = GPIO_NUM_9; // A

constexpr gpio_num_t SUCTION_PWM = GPIO_NUM_35;

#define SEN_R90 ADC2_CHANNEL_2
#define SEN_L90 ADC2_CHANNEL_4
#define SEN_R45 ADC2_CHANNEL_6
#define SEN_L45 ADC2_CHANNEL_7
#define BATTERY ADC2_CHANNEL_9

#define SEN_R90_GPIO GPIO_NUM_13
#define SEN_L90_GPIO GPIO_NUM_15
#define SEN_R45_GPIO GPIO_NUM_17
#define SEN_L45_GPIO GPIO_NUM_18
#define BATTERY_GPIO GPIO_NUM_20

#define MAX(a, b) ((a) > (b) ? (a) : (b))
#define MIN(a, b) ((a) < (b) ? (a) : (b))

// constexpr adc2_channel_t SEN_R90 = ADC2_CHANNEL_0;
// constexpr adc2_channel_t SEN_R45 = ADC2_CHANNEL_1;
// constexpr adc2_channel_t SEN_F = ADC2_CHANNEL_4;
// constexpr adc2_channel_t SEN_L45 = ADC2_CHANNEL_6;
// constexpr adc2_channel_t SEN_L90 = ADC2_CHANNEL_8;
// constexpr adc2_channel_t BATTERY = ADC2_CHANNEL_9;

constexpr int16_t ENCODER_H_LIM_VAL = 32767;
constexpr int16_t ENCODER_L_LIM_VAL = -32767;

const int16_t ENC_RESOLUTION = 16384 - 1;
constexpr uint8_t READ_FLAG = 0x80;
constexpr uint16_t READ_FLAG2 = 0b01000000;
constexpr uint16_t PARITY_FLAG = 0b10000000;
constexpr uint8_t ESC = 0x1B;
constexpr uint16_t BUF_SIZE = 4096;

constexpr uint16_t MOTION_CHECK_TH = 1000;
constexpr uint16_t ENC_OPE_V_R_TH = 175;

constexpr uint16_t LOG_SIZE = 1300;
constexpr uint16_t LINE_BUF_SIZE = 1024;
// constexpr float BATTERY_GAIN = 3.2075; // 2.97324;
constexpr float BATTERY_GAIN = 3.317057486323464; // 2.97324;

constexpr uint8_t LEDC_HIGH_SPEED_MODE = 0;
constexpr float LOW_BATTERY_TH = 11.7;

constexpr uint16_t RESET_GYRO_LOOP_CNT = 512;

static const std::string slalom_log_file("/spiflash/sla.log");
static const std::string sysid_log_file("/spiflash/sysid.log");
static const std::string maze_log_file("/spiflash/maze.txt");
static const std::string maze_log_kata_file("/spiflash/maze_kata.log");
static const std::string maze_log_return_file("/spiflash/maze_return.log");

static const std::string format1("%d,%0.3f,%0.3f,%0.3f,%0.3f,%0.3f,%d,%d,%0.3f,"
                                 "%0.3f,%0.3f,%0.3f,");
static const std::string
    format2("%0.3f,%0.3f,%0.3f,%0.3f,%0.3f,%0.3f,%0.3f,%0.3f,%0.3f,");
static const std::string format3("%0.3f,%0.3f,%0.3f,%0.3f,%0.3f,%0.3f,%0.3f,%0."
                                 "3f,%0.3f,%0.3f,%0.3f,%0.3f,%0.3f,%0.3f,%0.3f,"
                                 "%0.3f,%d,");
static const std::string format4("%0.3f,%0.3f,%0.3f,%0.3f,%d,%d,%d,%d,%d,%d,");
static const std::string format5(
    "%0.3f,%0.3f,%0.3f,%0.3f,%0.3f,%0.3f,%0.3f,%0.3f,%0.3f,%0.3f,%0.3f,%0.3f,");
static const std::string format6(
    "%0.3f,%0.3f,%0.3f,%0.3f,%0.3f,%0.3f,%0.3f,%0.3f,%0.3f,%0.3f,%0.3f,%0.3f,");
static const std::string format7("%0.3f,%0.3f,%0.3f,%0.3f\n");
static const std::string
    formatsysid("%d,%0.3f,%0.3f,%0.3f,%0.3f,%0.3f,%0.3f\n");
static char line_buf[LINE_BUF_SIZE];
// static const std::string format1("%d,%d,%d,%d,%d,%d,");
// static const std::string format2("%d,%d,%d,%d,%d,%d,%d,");
// static const std::string format3("%d,%d,%d,%d,%d,%d,%d,%d,%d,%d,%d,%d\n");

std::shared_ptr<sensing_result_entity_t> get_sensing_entity();

#endif

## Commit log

2023-03-25 cp Exia7th
2023-06-12 sensing_taskをRTOSから離脱
2023-06-26 add eigen
2023-08-01 add 調整手順
2023-08-01 update param
2023-08-01 update 区画中心調整
2023-08-01 update 前壁制御調整
2023-08-21 upadte
2023-08-21 refactor
2023-09-08 feat: kanazawa
2023-09-18 2023.09.10 kanazawa
2023-09-28 tuning
2023-10-01 tune dia45
2023-10-08 20231008_tohoku
2023-11-03 update for chubu
2023-11-26 update for BansheeAlter
2023-12-09 feat: pid gain plot
2023-12-13 feat: add classic mode
2024-01-28 bugfix
2024-02-06 update orval
2024-02-08 update: large90
2024-02-11 update chubu
2024-02-14 feat; load default param
2024-02-16 update: readme
2024-02-16 docs: update
2024-02-17 docs: add matlab doc
2024-07-27 update for IRAM_ATTR
2024-08-05 update IRAM_ATTR
2024-09-05 update for sensing faster
2024-09-17 update 0917
2024-09-17 update sdkconfig
2024-09-19 update params
2024-09-19 update robust maze sover
2024-09-26 update for hokushinetsu
